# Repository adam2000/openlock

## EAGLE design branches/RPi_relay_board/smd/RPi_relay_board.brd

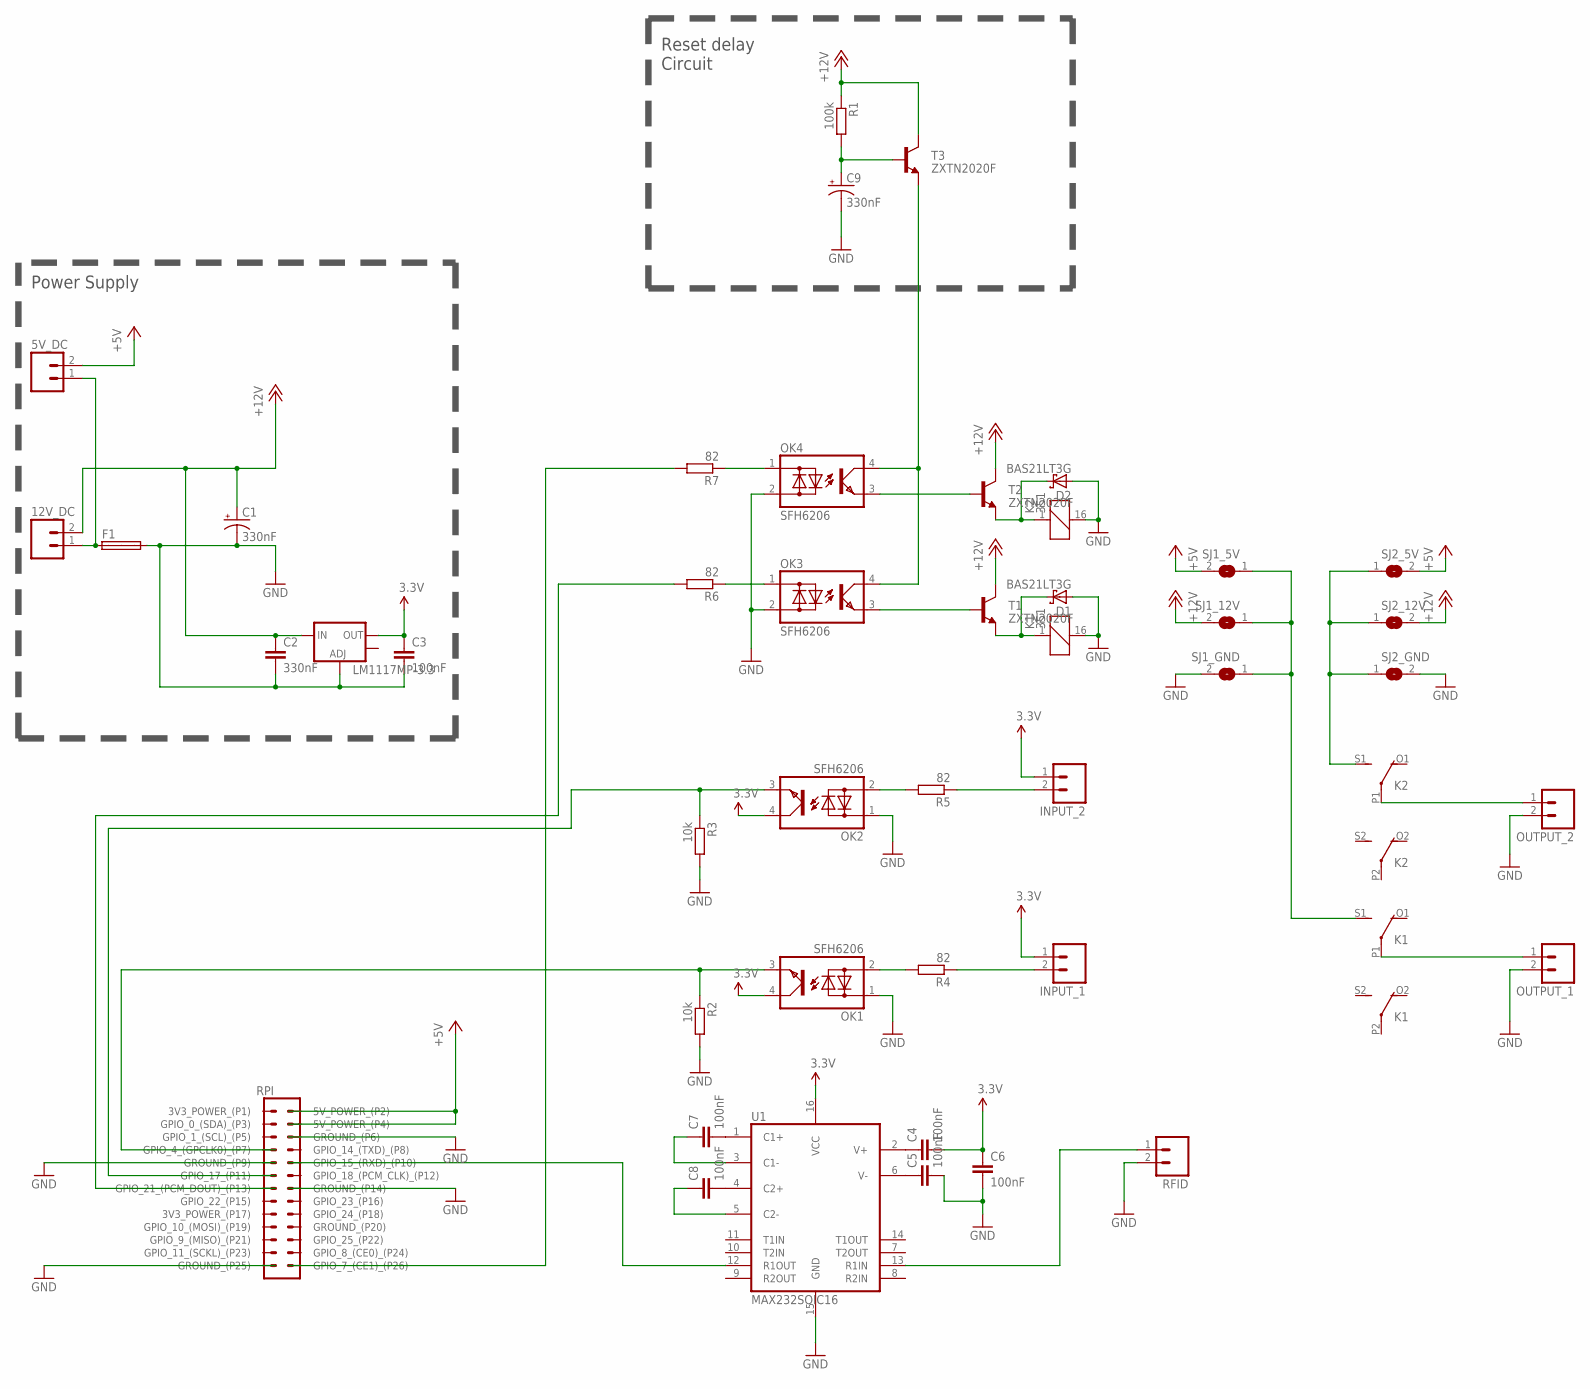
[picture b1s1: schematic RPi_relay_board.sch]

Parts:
5V_DC, 12V_DC: M02PTH3_5MM; 1X02_LONGPADS
C1, C9: 330nF; EIA7343
C2: 330nF; C3216
C3: 100nF; C3216
C4, C5, C6, C7, C8: 100nF; C2012
D1, D2: BAS21LT3G; SOT23
F1: SHK20L
INPUT_1, INPUT_2: M02PTH3_5MM; 1X02_LONGPADS
K1, K2: 351
LM1117MP-3.3: V_REG_LM1117SOT223; SOT223
OK1, OK2, OK3, OK4: SFH6206; DIL4-SMD
OUTPUT_1, OUTPUT_2: M02PTH3_5MM; 1X02_LONGPADS
R1: 100k; M0805
R2, R3: 10k; M0805
R4, R5, R6, R7: 82; M0805
RFID: M02PTH3_5MM; 1X02_LONGPADS
RPI: PINHD-2X13; 2X13
SJ1_5V, SJ1_12V, SJ1_GND, SJ2_5V, SJ2_12V, SJ2_GND: SJW
T1, T2, T3: ZXTN2020F; SOT23
U1: MAX232SOIC16; SO016

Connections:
3.3V: C3.1, C4.2, C6.1, INPUT_1.1, INPUT_2.1, LM1117MP-3.3.2 (OUT), OK1.4 (C), OK2.4 (C), U1.16 (VCC)
+5V: 5V_DC.2, RPI.2 (5V_POWER_(P2)), RPI.4 (5V_POWER_(P4)), SJ1_5V.2, SJ2_5V.2
+12V: 12V_DC.2, C1.A (+), C2.1, LM1117MP-3.3.3 (IN), R1.1, SJ1_12V.2, SJ2_12V.2, T1.3 (C), T2.3 (C), T3.3 (C)
GND: C1.C (-), C2.2, C3.2, C5.2, C6.2, C9.C (-), D1.1 (A), D2.1 (A), F1.2A, K1.16 (2), K2.16 (2), LM1117MP-3.3.1 (ADJ), OK1.1 (AC1), OK2.1 (AC1), OK3.2 (AC2), OK4.2 (AC2), OUTPUT_1.2, OUTPUT_2.2, R2.2, R3.2, RFID.2, RPI.6 (GROUND_(P6)), RPI.9 (GROUND_(P9)), RPI.14 (GROUND_(P14)), RPI.25 (GROUND_(P25)), SJ1_GND.2, SJ2_GND.2, U1.15 (GND)
unnamed: OK2.3 (E), R3.1, RPI.11 (GPIO_17_(P11))
unnamed: OK1.2 (AC2), R4.2
unnamed: INPUT_1.2, R4.1
unnamed: OK1.3 (E), R2.1, RPI.7 (GPIO_4_(GPCLK0)_(P7))
unnamed: INPUT_2.2, R5.1
unnamed: R7.2, RPI.26 (GPIO_7_(CE1)_(P26))
unnamed: OK4.3 (E), T2.1 (B)
unnamed: OK3.3 (E), T1.1 (B)
unnamed: OK2.2 (AC2), R5.2
unnamed: C9.A (+), R1.2, T3.1 (B)
unnamed: D2.3 (C), K2.1, T2.2 (E)
unnamed: D1.3 (C), K1.1, T1.2 (E)
unnamed: C7.2, U1.1 (C1+)
unnamed: OK3.4 (C), OK4.4 (C), T3.2 (E)
unnamed: RPI.10 (GPIO_15_(RXD)_(P10)), U1.12 (R1OUT)
unnamed: RFID.1, U1.13 (R1IN)
unnamed: 5V_DC.1, 12V_DC.1, F1.1A
unnamed: K2.S1 (S), SJ2_5V.1, SJ2_12V.1, SJ2_GND.1
unnamed: OK4.1 (AC1), R7.1
unnamed: K1.S1 (S), SJ1_5V.1, SJ1_12V.1, SJ1_GND.1
unnamed: K2.P1, OUTPUT_2.1
unnamed: K1.P1, OUTPUT_1.1
unnamed: C8.2, U1.4 (C2+)
unnamed: C7.1, U1.3 (C1-)
unnamed: C8.1, U1.5 (C2-)
unnamed: C4.1, U1.2 (V+)
unnamed: C5.1, U1.6 (V-)
unnamed: R6.2, RPI.13 (GPIO_21_(PCM_DOUT)_(P13))
unnamed: OK3.1 (AC1), R6.1

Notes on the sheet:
Reset delay Circuit
Power Supply

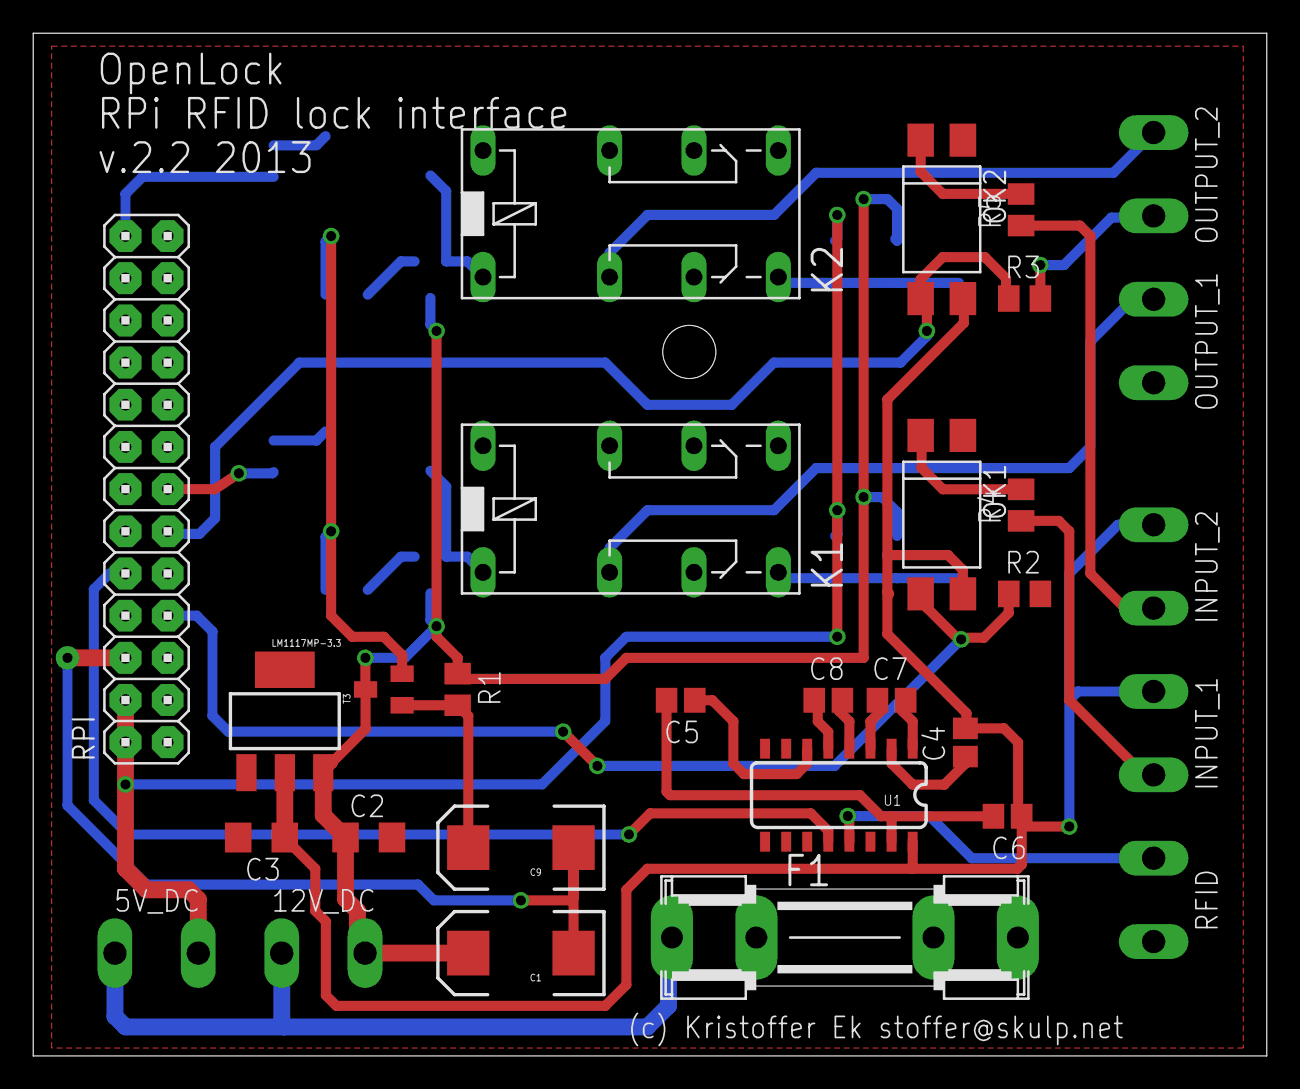
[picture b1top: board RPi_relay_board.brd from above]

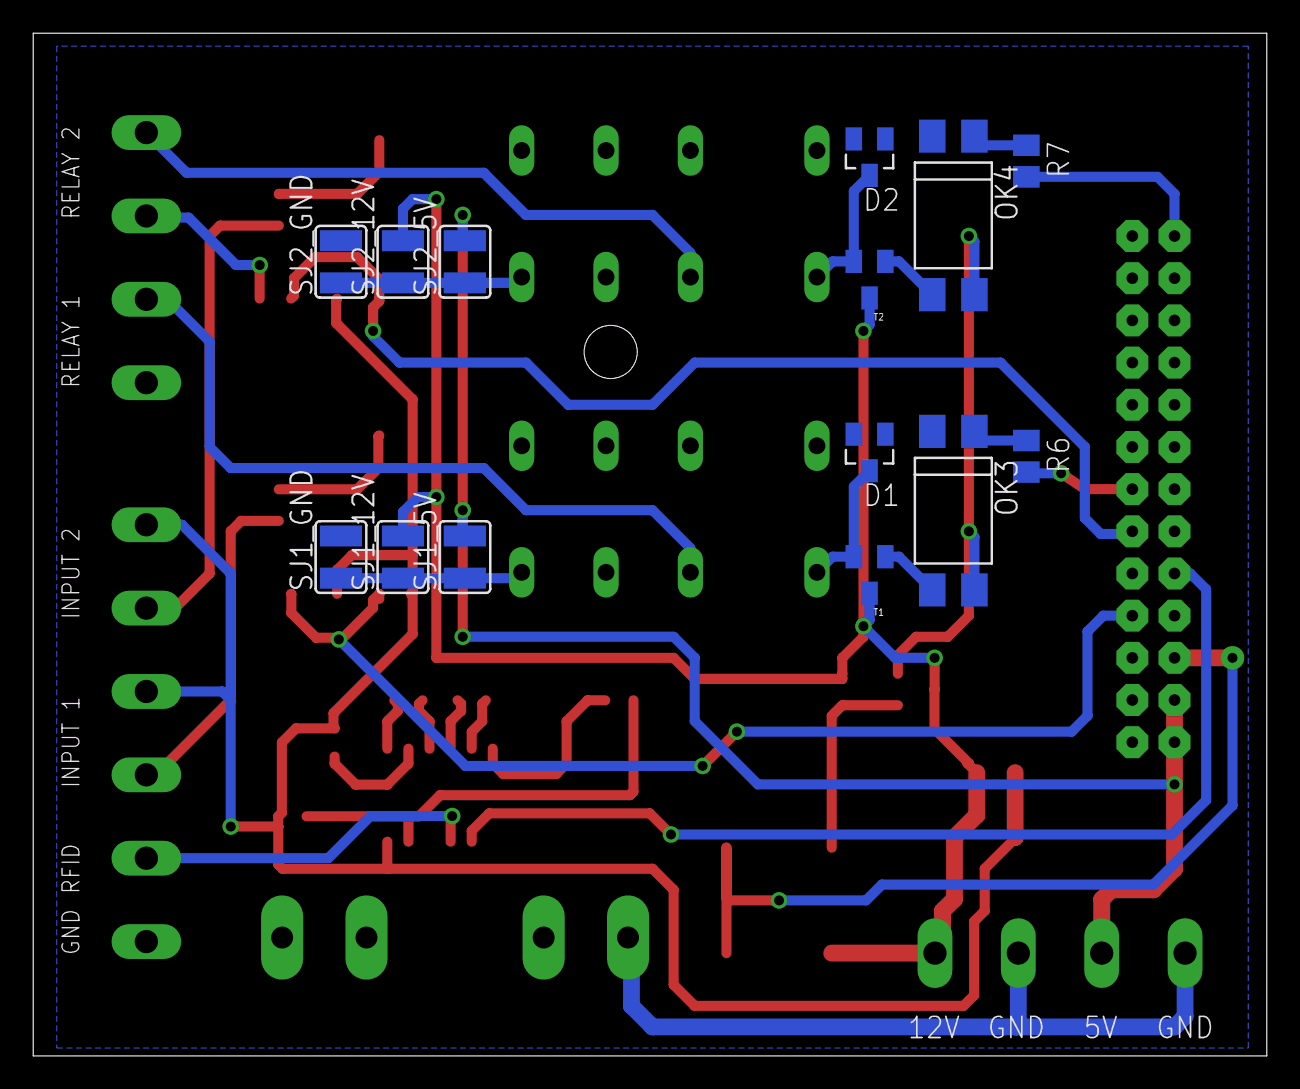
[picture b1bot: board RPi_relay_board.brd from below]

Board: 2 copper layers, 74.3 x 61.6 mm, 44 parts (14 on the bottom side), 33 nets.

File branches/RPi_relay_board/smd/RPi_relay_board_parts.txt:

Part         Value          Device              Package       Library     Sheet

5V_DC                       M02PTH3_5MM         1X02_LONGPADS SparkFun    1
12V_DC                      M02PTH3_5MM         1X02_LONGPADS SparkFun    1
C1           330nF          CAP_POL7343         EIA7343       SparkFun    1
C2           330nF          C-EUC3216           C3216         rcl         1
C3           100nF          C-EUC3216           C3216         rcl         1
C4           100nF          C-EUC2012           C2012         rcl         1
C5           100nF          C-EUC2012           C2012         rcl         1
C6           100nF          C-EUC2012           C2012         rcl         1
C7           100nF          C-EUC2012           C2012         rcl         1
C8           100nF          C-EUC2012           C2012         rcl         1
C9           330nF          CAP_POL7343         EIA7343       SparkFun    1
D1           BAS21LT3G      BAS40               SOT23         diode       1
D2           BAS21LT3G      BAS40               SOT23         diode       1
F1                          SHK20L              SHK20L        fuse        1
INPUT_1                     M02PTH3_5MM         1X02_LONGPADS SparkFun    1
INPUT_2                     M02PTH3_5MM         1X02_LONGPADS SparkFun    1
K1           351            351                 351           relay       1
K2           351            351                 351           relay       1
LM1117MP-3.3                V_REG_LM1117SOT223  SOT223        SparkFun    1
OK1          SFH6206        SFH6206             DIL4-SMD      optocoupler 1
OK2          SFH6206        SFH6206             DIL4-SMD      optocoupler 1
OK3          SFH6206        SFH6206             DIL4-SMD      optocoupler 1
OK4          SFH6206        SFH6206             DIL4-SMD      optocoupler 1
OUTPUT_1                    M02PTH3_5MM         1X02_LONGPADS SparkFun    1
OUTPUT_2                    M02PTH3_5MM         1X02_LONGPADS SparkFun    1
R1           100k           R-EU_M0805          M0805         rcl         1
R2           10k            R-EU_M0805          M0805         rcl         1
R3           10k            R-EU_M0805          M0805         rcl         1
R4           82             R-EU_M0805          M0805         rcl         1
R5           82             R-EU_M0805          M0805         rcl         1
R6           82             R-EU_M0805          M0805         rcl         1
R7           82             R-EU_M0805          M0805         rcl         1
RFID                        M02PTH3_5MM         1X02_LONGPADS SparkFun    1
RPI                         PINHD-2X13          2X13          RPi_pinhead 1
T1           ZXTN2020F      TRANSISTOR_NPNSOT23 SOT23         SparkFun    1
T2           ZXTN2020F      TRANSISTOR_NPNSOT23 SOT23         SparkFun    1
T3           ZXTN2020F      TRANSISTOR_NPNSOT23 SOT23         SparkFun    1
U1           MAX232SOIC16   MAX232SOIC16        SO016         SparkFun    1

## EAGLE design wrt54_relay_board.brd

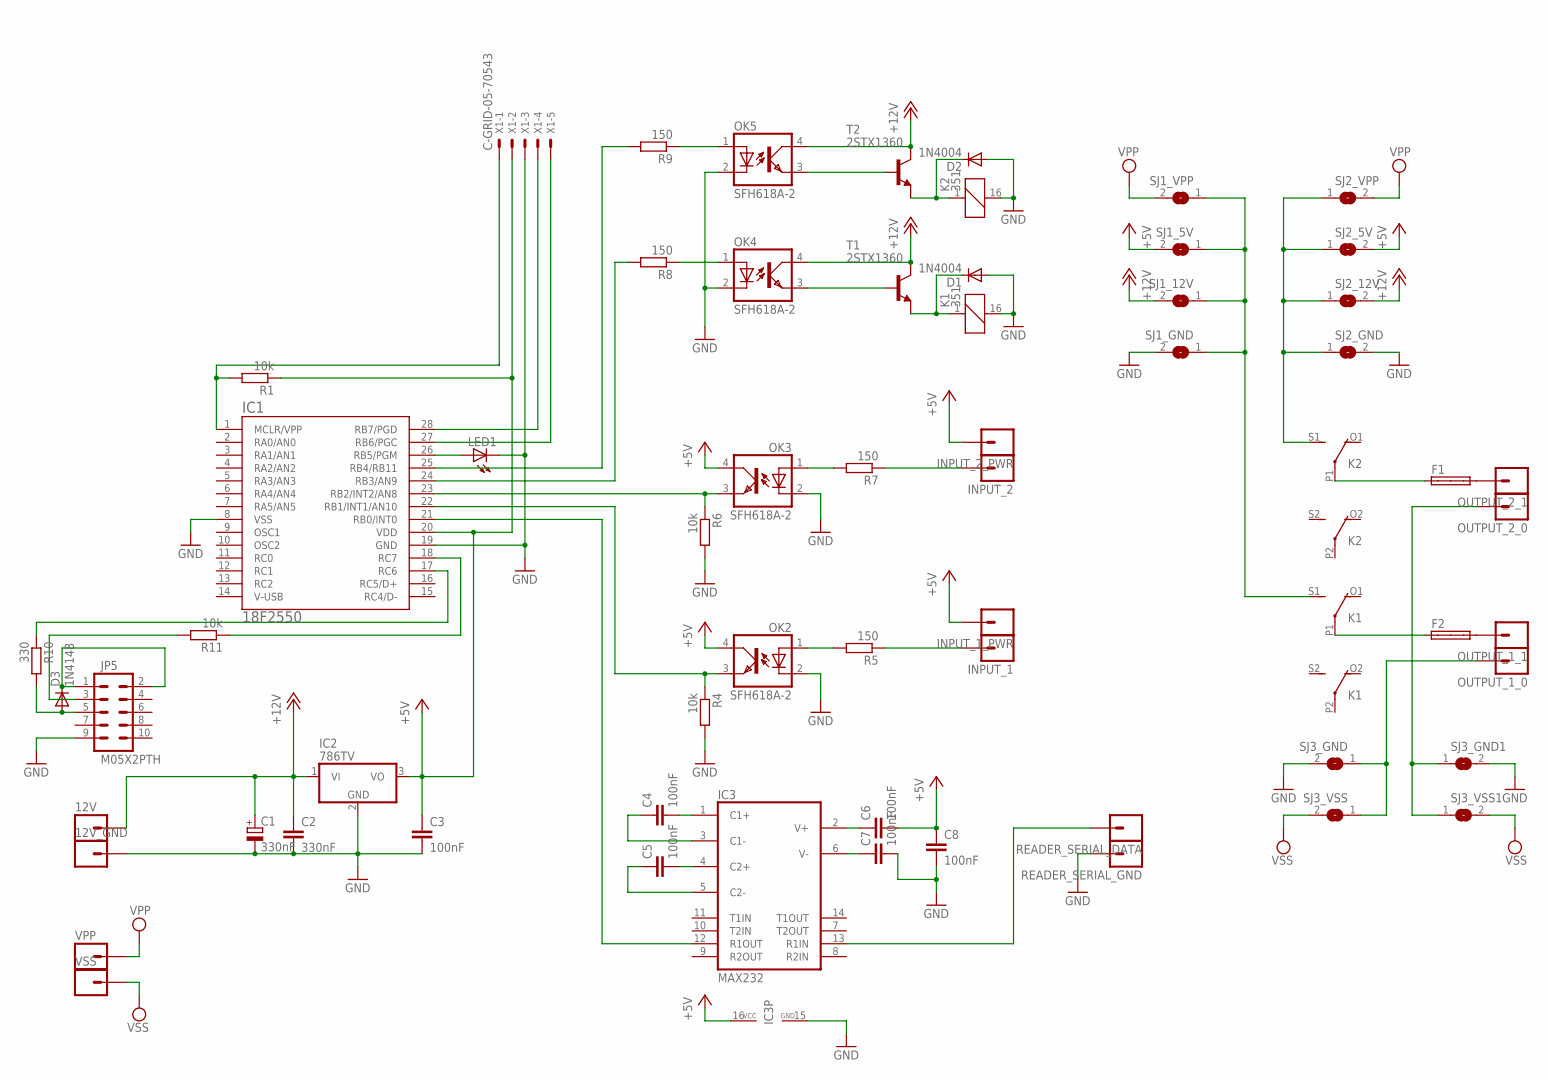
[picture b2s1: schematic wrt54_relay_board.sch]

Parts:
12V, 12V_GND: M01PTH_LONGPAD; 1X01_LONGPAD
C1: 330nF; E5-6
C2: 330nF; C5B2.5
C3, C4, C5, C6, C7, C8: 100nF; C5B2.5
D1, D2: 1N4004; DO35-7
D3: 1N4148; DO35-7
F1, F2: SHK20L
IC1: 18F2550; DIL28
IC2: 786TV; TO220V
IC3: MAX232; DIL16
INPUT_1, INPUT_1_PWR, INPUT_2, INPUT_2_PWR: M01PTH_LONGPAD; 1X01_LONGPAD
JP5: M05X2PTH; AVR_ICSP
K1, K2: 351
LED1: LED5MM
OK2, OK3, OK4, OK5: SFH618A-2; DIP4
OUTPUT_1_0, OUTPUT_1_1, OUTPUT_2_0, OUTPUT_2_1: M01PTH_LONGPAD; 1X01_LONGPAD
R1: 10k; 0204/7
R4, R6: 10k; 0207/10
R5, R7: 150; 0204V
R8, R9: 150; 0204/7
R10: 330; 0204V
R11: 10k; 0204V
READER_SERIAL_DATA: M01PTH_LONGPAD; 1X01_LONGPAD
READER_SERIAL_GND: M01PTH_LONGPAD; 1X01_LONGPAD
SJ1_5V, SJ1_12V, SJ1_GND, SJ1_VPP, SJ2_5V, SJ2_12V, SJ2_GND, SJ2_VPP, SJ3_GND, SJ3_GND1, SJ3_VSS, SJ3_VSS1: SJW
T1, T2: 2STX1360; TO92-ECB
VPP: M01PTH_LONGPAD; 1X01_LONGPAD
VSS: M01PTH_LONGPAD; 1X01_LONGPAD
X1: C-GRID-05-70543; 70543-05

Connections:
+5V: C3.1, C6.2, C8.1, IC1.20 (VDD), IC2.3 (VO), IC3.16 (VCC), INPUT_1_PWR.1, INPUT_2_PWR.1, OK2.4 (COL), OK3.4 (COL), R1.1, SJ1_5V.2, SJ2_5V.2, X1.2
+12V: 12V.1, C1.+, C2.1, IC2.1 (VI), OK4.4 (COL), OK5.4 (COL), SJ1_12V.2, SJ2_12V.2, T1.C, T2.C
GND: 12V_GND.1, C1.-, C2.2, C3.2, C7.2, C8.2, D1.A, D2.A, IC1.8 (VSS), IC1.19 (GND), IC2.2 (GND), IC3.15 (GND), JP5.9, K1.16 (2), K2.16 (2), LED1.K (C), OK2.2 (C), OK3.2 (C), OK4.2 (C), OK5.2 (C), R4.2, R6.2, READER_SERIAL_GND.1, SJ1_GND.2, SJ2_GND.2, SJ3_GND.2, SJ3_GND1.2, X1.3
unnamed: IC1.23 (RB2/INT2/AN8), OK3.3 (EMIT), R6.1
unnamed: OK2.1 (A), R5.2
unnamed: INPUT_1.1, R5.1
unnamed: IC1.22 (RB1/INT1/AN10), OK2.3 (EMIT), R4.1
unnamed: INPUT_2.1, R7.1
unnamed: IC1.25 (RB4/RB11), R9.2
unnamed: OK5.3 (EMIT), T2.B
unnamed: OK4.3 (EMIT), T1.B
unnamed: IC1.28 (RB7/PGD), X1.4
unnamed: IC1.1 (MCLR/VPP), R1.2, X1.1
unnamed: D2.C, K2.1, T2.E
unnamed: D1.C, K1.1, T1.E
unnamed: C4.2, IC3.1 (C1+)
unnamed: IC1.26 (RB5/PGM), LED1.A
unnamed: IC1.21 (RB0/INT0), IC3.12 (R1OUT)
unnamed: IC3.13 (R1IN), READER_SERIAL_DATA.1
unnamed: OK3.1 (A), R7.2
unnamed: K2.S1 (S), SJ2_5V.1, SJ2_12V.1, SJ2_GND.1, SJ2_VPP.1
unnamed: OK5.1 (A), R9.1
unnamed: K1.S1 (S), SJ1_5V.1, SJ1_12V.1, SJ1_GND.1, SJ1_VPP.1
unnamed: F1.2A, OUTPUT_2_1.1
unnamed: F2.2A, OUTPUT_1_1.1
unnamed: OUTPUT_1_0.1, SJ3_GND.1, SJ3_VSS.1
unnamed: IC1.17 (RC6), R10.1
unnamed: IC1.18 (RC7), R11.1
unnamed: OUTPUT_2_0.1, SJ3_GND1.1, SJ3_VSS1.1
unnamed: F1.1A, K2.P1
unnamed: F2.1A, K1.P1
unnamed: C5.2, IC3.4 (C2+)
unnamed: C4.1, IC3.3 (C1-)
unnamed: D3.C, JP5.1, JP5.2
unnamed: D3.A, JP5.5, R10.2
unnamed: C5.1, IC3.5 (C2-)
unnamed: C6.1, IC3.2 (V+)
unnamed: C7.1, IC3.6 (V-)
unnamed: JP5.3, R11.2
unnamed: IC1.24 (RB3/AN9), R8.2
unnamed: OK4.1 (A), R8.1
unnamed: IC1.27 (RB6/PGC), X1.5
VPP: SJ1_VPP.2, SJ2_VPP.2, VPP.1
VSS: SJ3_VSS.2, SJ3_VSS1.2, VSS.1

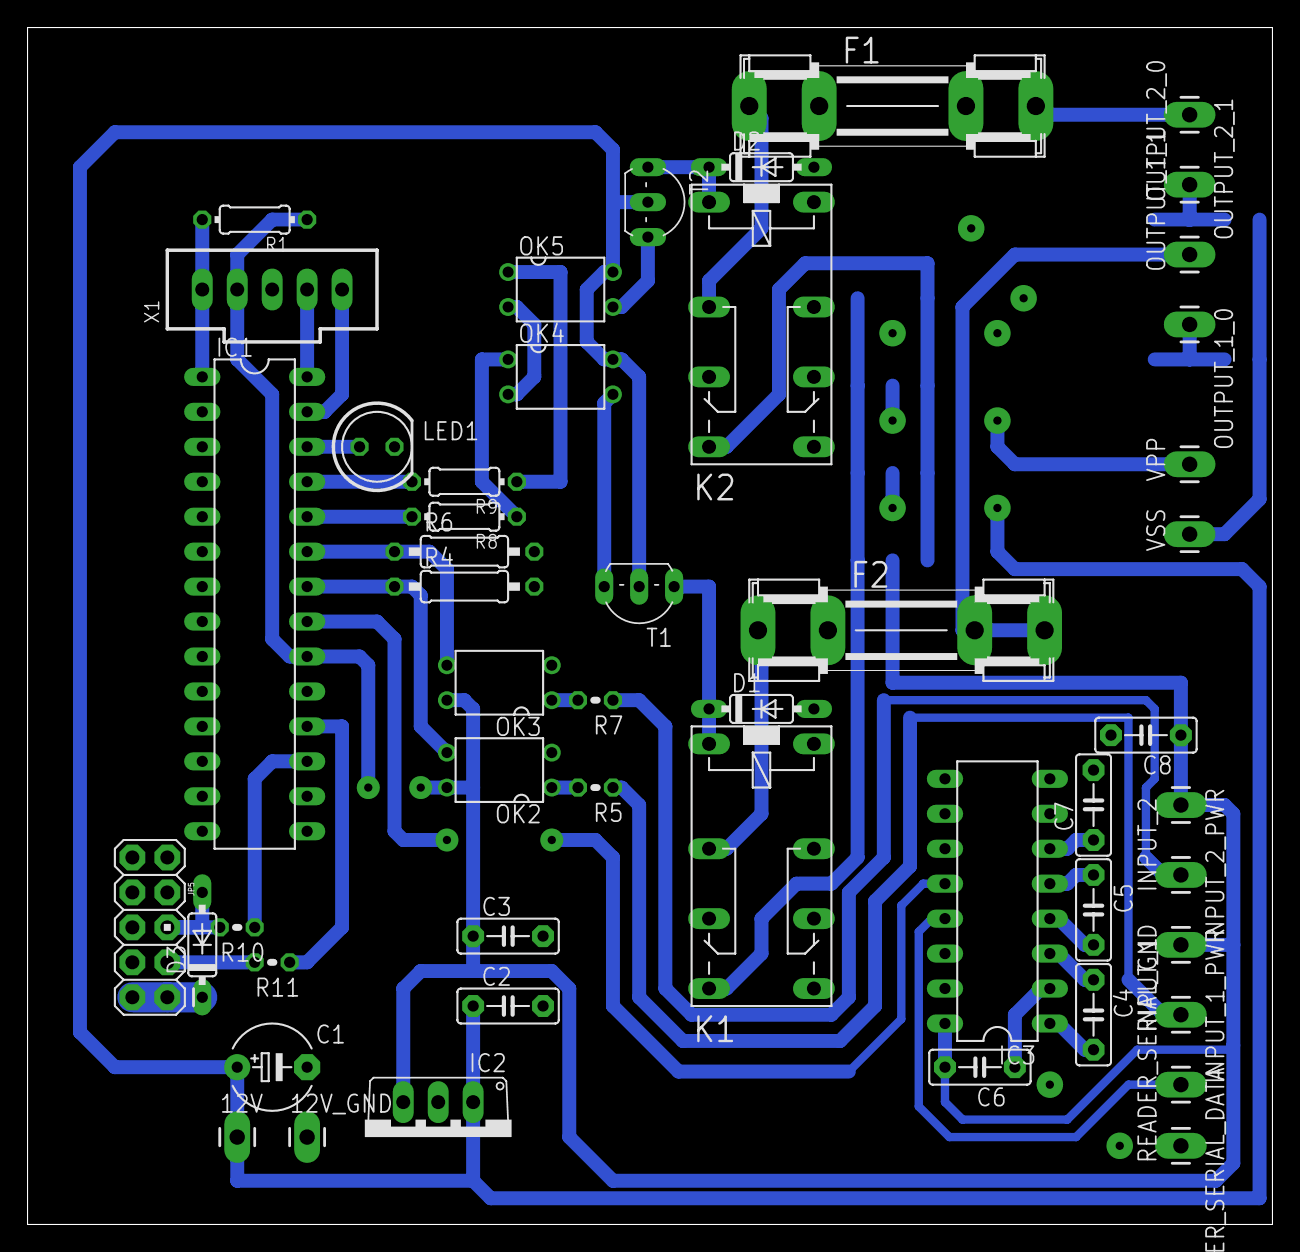
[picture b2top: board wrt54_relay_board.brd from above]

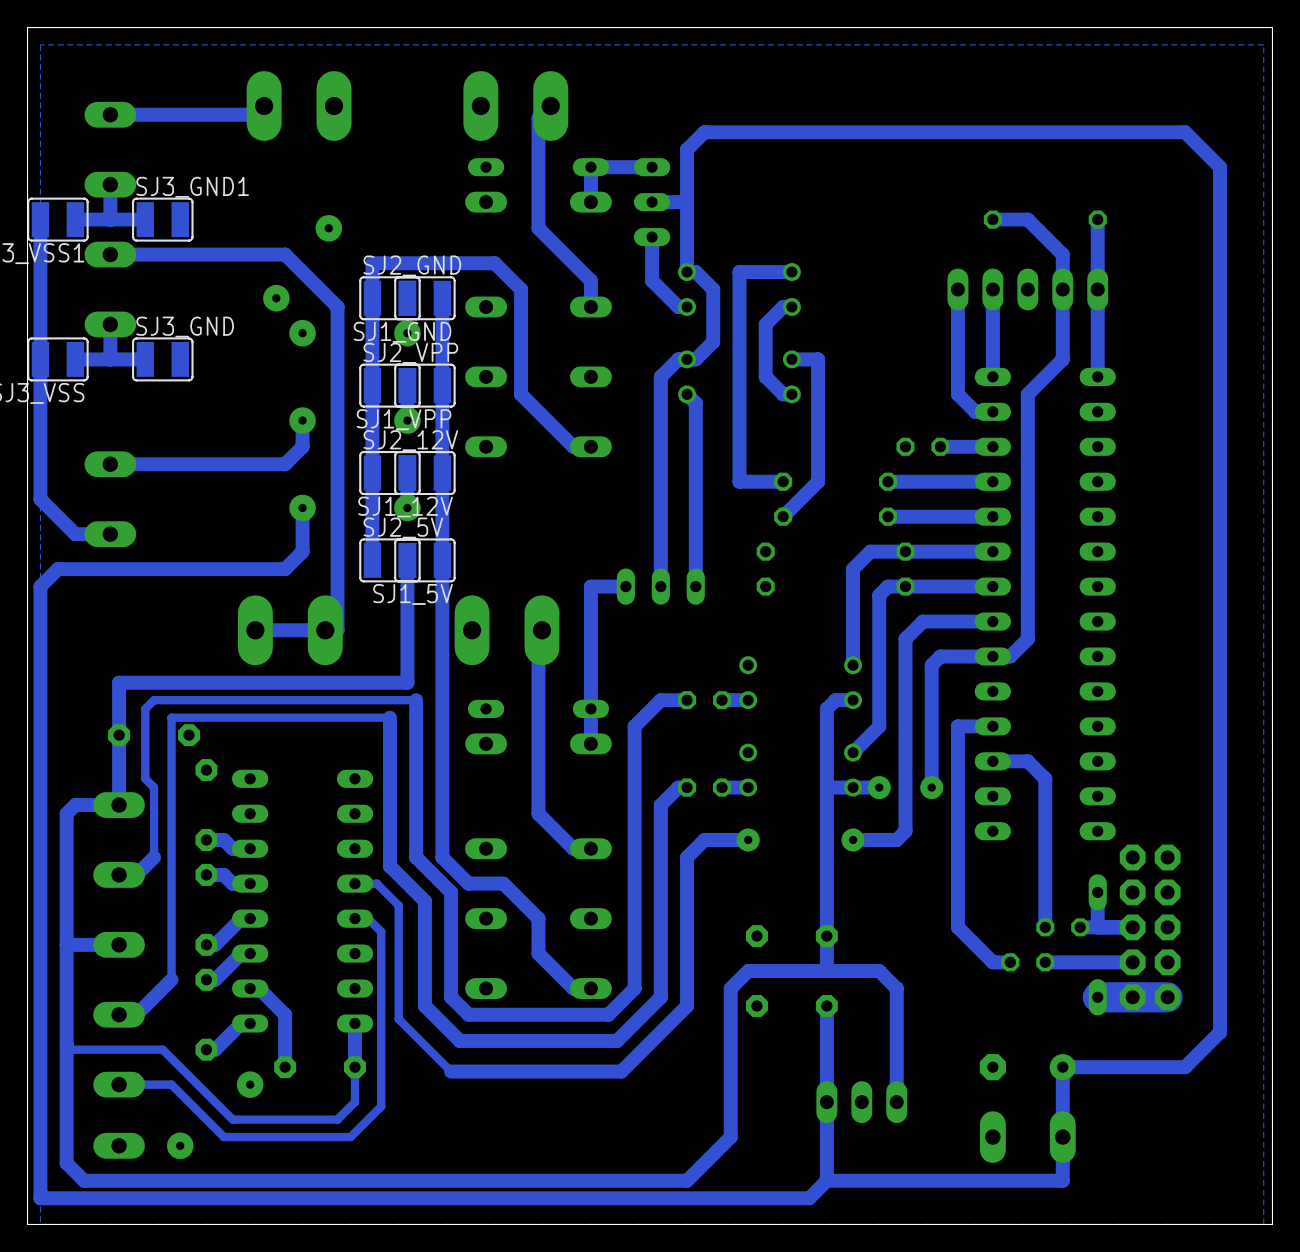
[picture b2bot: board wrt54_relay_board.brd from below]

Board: 2 copper layers, 90.5 x 87.0 mm, 62 parts (12 on the bottom side), 44 nets.

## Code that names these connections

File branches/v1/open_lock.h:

// IO constants
#define RFID_IN_PIN			PORTBbits.RB0
#define INPUT_1_PIN			PORTBbits.RB1
#define INPUT_2_PIN			PORTBbits.RB2
#define RELAY_1_PIN			PORTBbits.RB3
#define RELAY_2_PIN			PORTBbits.RB4
#define LED_PIN					PORTBbits.RB5
#define TX_PIN					PORTCbits.RC6
#define RX_PIN					PORTCbits.RC7

#define TRIS_RFID_IN		TRISBbits.TRISB0
#define TRIS_INPUT_1		TRISBbits.TRISB1
#define TRIS_INPUT_2		TRISBbits.TRISB2
#define TRIS_RELAY_1		TRISBbits.TRISB3
#define TRIS_RELAY_2		TRISBbits.TRISB4
#define TRIS_LED				TRISBbits.TRISB5

#define TRIS_TX					TRISCbits.TRISC6
#define TRIS_RX					TRISCbits.TRISC7

// Protocol constants
#define OPEN_DOOR 'o'
#define RELAY_1_ON 'p'
#define RELAY_2_ON 'q'
#define RELAY_1_OFF 'r'
#define RELAY_2_OFF 's'
#define DUMP_RFIDS 'x'
#define FLUSH_RFIDS 'z'

#define INPUT_1 't'
#define INPUT_2 'u'

#define DOOR_OPEN_TIME 2000	// 2 sec

#define RFID_LENGTH 10
#define COMMAND_LENGTH 10
#define MAX_USERS 20

// soft uart stuff
#define BAUD_RATE		9200

#define SER_BAUD 103

#define TIMER2_RELOAD 0x31		// 1 ms @ 8MHz

void sleep_ms(unsigned long ms);

static void high_priority_isr(void) __interrupt 1;
static void low_priority_isr(void) __interrupt 2;

void my_usart_open();

void led_debug();
void open_door();

unsigned char fifo_in_use();
unsigned char fifo_put(unsigned char c);
unsigned char fifo_get(unsigned char *c);

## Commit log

2012-01-29 Initial directory structure.
2012-01-29 initial version
2012-01-29 possible missaligning start-bit
2012-01-30 Fully working soft uart and some lock-checking
    Needs to implement uploading of keys
2012-01-30 working serial upload of rfid-keys
2012-01-30 testing...
2012-02-01 simple protocol for upload of rfid keys
2012-02-01 added missing resistor between wrt54-tx and pic-rx - it burned the tx port twice :-(
    added flush command to delete all rfid
2012-02-01 use fifo buffer
2012-02-01 init fifo head and tail
2012-02-01 test
2012-02-01 almost working with fifo-code
    can add rfids
2012-02-01 working with fifo
2012-02-01 cleanup
2012-02-01 more cleanup + larger memory
2012-02-01 linker script
2012-02-01 simons kloge forbedringer
2012-03-13 smaller board layout
2013-04-26 first public version
2013-04-26 dbi username/password moved to common module
2013-04-26 more cleanup
2013-04-26 working (no db password in code)
2013-04-27 xml::rpc replaced by AnyEvent::JSONRPC
2013-04-27 sleep in main loop to lower cpu load
2013-04-27 lock_server.pl split up to single thread processes
2013-04-27 bugfix
2013-04-27 not used any more
2013-04-27 apache conf + lockserver modperl
2013-04-27 Version 1.x-series of pcb
2013-04-27 Version 2.0-series of pcb
2013-04-27 pdf previews of .brd
2013-04-27 exported partlist for documentation
2013-04-28 updated to rev b RPi
2013-04-28 input opto's was wrong polarity on output
2013-04-28 small corrections
2013-04-28 pdf previews of pcb v2.2
2013-04-29 smaller pcb, so it fits in RS 458-0768
2013-04-30 didn't activate LED relay
2013-04-30 load some modules at startup
2013-04-30 more module load at startup
2013-04-30 button working
2013-05-04 indicate lock status on tp-link led
2013-05-04 mysql_auto_reconnect in global db connect
2013-05-07 sig int handler working
2013-05-24 command line util to unlock
2013-06-01 play audio on open
2013-06-01 enable sound on open
2013-06-15 support for remote master lock
2013-06-15 group name in db prefs
2013-06-15 killall -USR1 update_master_lock.pl to force update remote master
2013-09-06 drop junk characters received over serial rfid
2014-10-06 connect error handling
2016-05-07 Migrating wiki contents from Google Code

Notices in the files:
parts and their libraries:
SparkFun: Licensing: CC v3.0 Share-Alike You are welcome to use this library for commercial purposes.
